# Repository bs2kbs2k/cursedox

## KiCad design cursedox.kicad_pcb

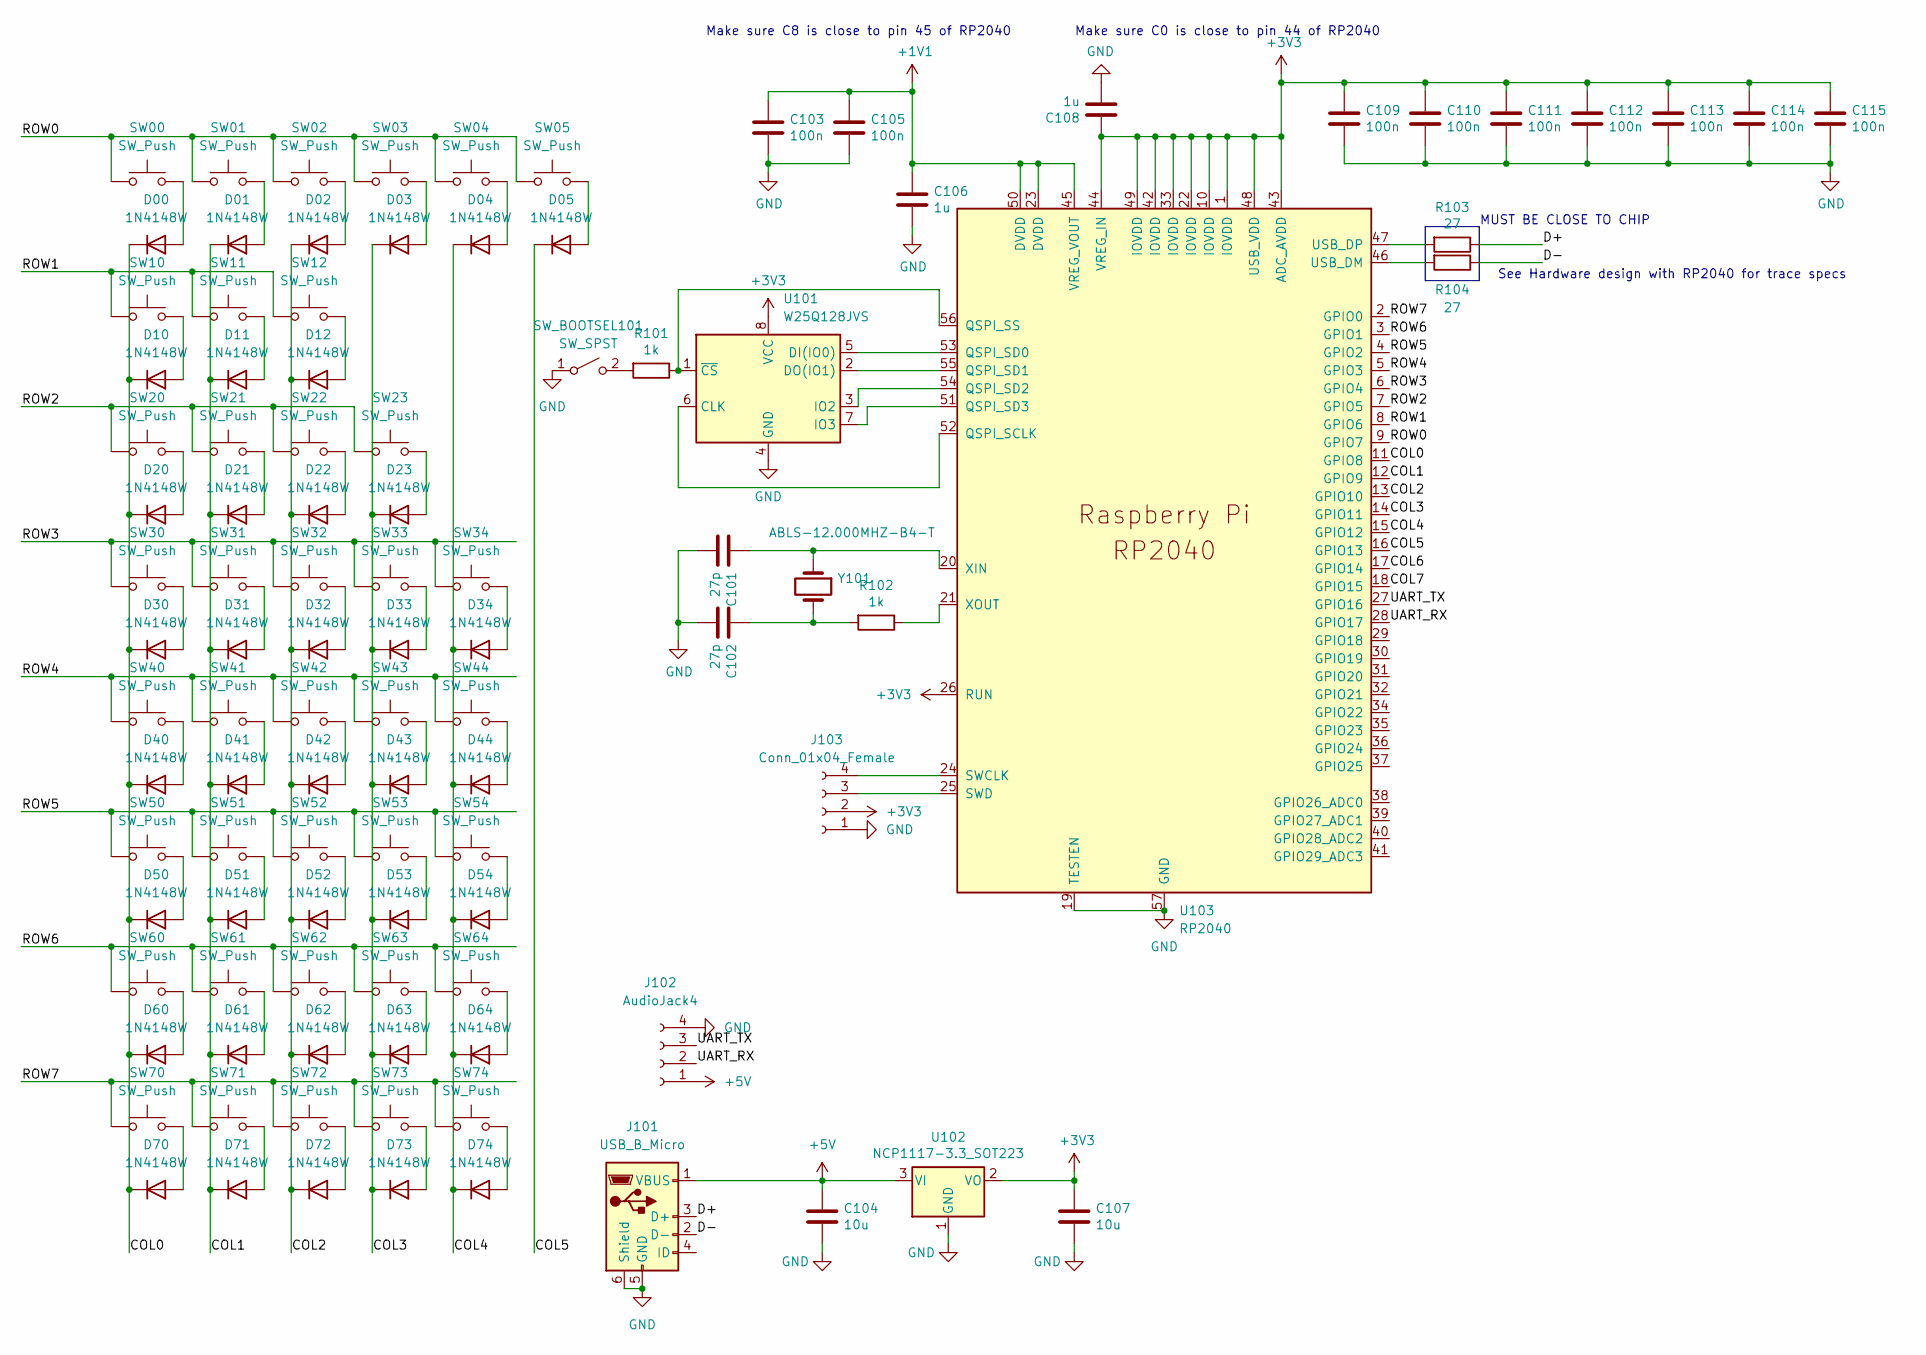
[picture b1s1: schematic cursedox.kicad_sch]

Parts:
C101, C102: 27p; C_0402_1005Metric
C103, C105, C109, C110, C111, C112, C113, C114, C115: 100n; C_0402_1005Metric
C104, C107: 10u; C_0805_2012Metric
C106, C108: 1u; C_0402_1005Metric
D00, D01, D02, D03, D04, D05, D10, D11, D12, D20, D21, D22, D23, D30, D31, D32, D33, D34, D40, D41, D42, D43, D44, D50, D51, D52, D53, D54, D60, D61, D62, D63, D64, D70, D71, D72, D73, D74: 1N4148W; D_SOD-123
J101: USB_B_Micro; USB_Micro-B_Molex-105017-0001
J102: AudioJack4; Molex_Pico-Clasp_202396-0407_1x04-1MP_P1.00mm_Horizontal
J103: Conn_01x04_Female; PinHeader_1x04_P2.54mm_Vertical
R101, R102: 1k; C_0402_1005Metric
R103, R104: 27; C_0402_1005Metric
SW00, SW01, SW02, SW03, SW10, SW20, SW21, SW22, SW23, SW30, SW31, SW32, SW33, SW34, SW40, SW41, SW42, SW43, SW44, SW50, SW51, SW52, SW53, SW54, SW60, SW61, SW62, SW63, SW64, SW74: SW_Push; SW_Hotswap_Kailh_MX_1.00u
SW04, SW05: SW_Push; SW_Hotswap_Kailh_MX_2.00u_90deg
SW11, SW12: SW_Push; SW_Hotswap_Kailh_MX_1.50u_90deg
SW70, SW71, SW72, SW73: SW_Push; SW_Hotswap_Kailh_MX_1.50u
SW_BOOTSEL101: SW_SPST; SW_TH_Tactile_Omron_B3F-10xx
U101: W25Q128JVS; SOIC-8_5.23x5.23mm_P1.27mm
U102: NCP1117-3.3_SOT223; SOT-223-3_TabPin2
U103: RP2040; RP2040-QFN-56
Y101: ABLS-12.000MHZ-B4-T; Crystal_SMD_HC49-US

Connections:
+1V1: C103.1, C105.1, C106.1, U103.23 (DVDD), U103.45 (VREG_VOUT), U103.50 (DVDD)
+3V3: C107.1, C108.1, C109.1, C110.1, C111.1, C112.1, C113.1, C114.1, C115.1, J103.2, U101.8 (VCC), U102.2 (VO), U103.1 (IOVDD), U103.10 (IOVDD), U103.22 (IOVDD), U103.26 (RUN), U103.33 (IOVDD), U103.42 (IOVDD), U103.43 (ADC_AVDD), U103.44 (VREG_IN), U103.48 (USB_VDD), U103.49 (IOVDD)
+5V: C104.1, J101.1 (VBUS), J102.1, U102.3 (VI)
/COL0: D00.1 (K), D10.1 (K), D20.1 (K), D30.1 (K), D40.1 (K), D50.1 (K), D60.1 (K), D70.1 (K), U103.11 (GPIO8)
/COL1: D01.1 (K), D11.1 (K), D21.1 (K), D31.1 (K), D41.1 (K), D51.1 (K), D61.1 (K), D71.1 (K), U103.12 (GPIO9)
/COL2: D02.1 (K), D12.1 (K), D22.1 (K), D32.1 (K), D42.1 (K), D52.1 (K), D62.1 (K), D72.1 (K), U103.13 (GPIO10)
/COL3: D03.1 (K), D23.1 (K), D33.1 (K), D43.1 (K), D53.1 (K), D63.1 (K), D73.1 (K), U103.14 (GPIO11)
/COL4: D04.1 (K), D34.1 (K), D44.1 (K), D54.1 (K), D64.1 (K), D74.1 (K), U103.15 (GPIO12)
/COL5: D05.1 (K), U103.16 (GPIO13)
/COL6: U103.17 (GPIO14)
/COL7: U103.18 (GPIO15)
/D+: J101.3 (D+), R103.1
/D-: J101.2 (D-), R104.1
/ROW0: SW00.1, SW01.1, SW02.1, SW03.1, SW04.1, SW05.1, U103.9 (GPIO7)
/ROW1: SW10.1, SW11.1, SW12.1, U103.8 (GPIO6)
/ROW2: SW20.1, SW21.1, SW22.1, SW23.1, U103.7 (GPIO5)
/ROW3: SW30.1, SW31.1, SW32.1, SW33.1, SW34.1, U103.6 (GPIO4)
/ROW4: SW40.1, SW41.1, SW42.1, SW43.1, SW44.1, U103.5 (GPIO3)
/ROW5: SW50.1, SW51.1, SW52.1, SW53.1, SW54.1, U103.4 (GPIO2)
/ROW6: SW60.1, SW61.1, SW62.1, SW63.1, SW64.1, U103.3 (GPIO1)
/ROW7: SW70.1, SW71.1, SW72.1, SW73.1, SW74.1, U103.2 (GPIO0)
/UART_RX: J102.2, U103.28 (GPIO17)
/UART_TX: J102.3, U103.27 (GPIO16)
GND: C101.2, C102.2, C103.2, C104.2, C105.2, C106.2, C107.2, C108.2, C109.2, C110.2, C111.2, C112.2, C113.2, C114.2, C115.2, J101.5 (GND), J101.6 (Shield), J102.4, J103.1, SW_BOOTSEL101.1 (A), U101.4 (GND), U102.1 (GND), U103.19 (TESTEN), U103.57 (GND)
unnamed: C101.1, U103.20 (XIN), Y101.1
unnamed: C102.1, R102.2, Y101.2
unnamed: D00.2 (A), SW00.2
unnamed: D01.2 (A), SW01.2
unnamed: D02.2 (A), SW02.2
unnamed: D03.2 (A), SW03.2
unnamed: D04.2 (A), SW04.2
unnamed: D05.2 (A), SW05.2
unnamed: D10.2 (A), SW10.2
unnamed: D11.2 (A), SW11.2
unnamed: D12.2 (A), SW12.2
unnamed: D20.2 (A), SW20.2
unnamed: D21.2 (A), SW21.2
unnamed: D22.2 (A), SW22.2
unnamed: D23.2 (A), SW23.2
unnamed: D30.2 (A), SW30.2
unnamed: D31.2 (A), SW31.2
unnamed: D32.2 (A), SW32.2
unnamed: D33.2 (A), SW33.2
unnamed: D34.2 (A), SW34.2
unnamed: D40.2 (A), SW40.2
unnamed: D41.2 (A), SW41.2
unnamed: D42.2 (A), SW42.2
unnamed: D43.2 (A), SW43.2
unnamed: D44.2 (A), SW44.2
unnamed: D50.2 (A), SW50.2
unnamed: D51.2 (A), SW51.2
unnamed: D52.2 (A), SW52.2
unnamed: D53.2 (A), SW53.2
unnamed: D54.2 (A), SW54.2
unnamed: D60.2 (A), SW60.2
unnamed: D61.2 (A), SW61.2
unnamed: D62.2 (A), SW62.2
unnamed: D63.2 (A), SW63.2
unnamed: D64.2 (A), SW64.2
unnamed: D70.2 (A), SW70.2
unnamed: D71.2 (A), SW71.2
unnamed: D72.2 (A), SW72.2
unnamed: D73.2 (A), SW73.2
unnamed: D74.2 (A), SW74.2
unnamed: J103.3, U103.25 (SWD)
unnamed: J103.4, U103.24 (SWCLK)
unnamed: R101.1, U101.1 (~CS), U103.56 (QSPI_SS)
unnamed: R101.2, SW_BOOTSEL101.2 (B)
unnamed: R102.1, U103.21 (XOUT)
unnamed: R103.2, U103.47 (USB_DP)
unnamed: R104.2, U103.46 (USB_DM)
unnamed: U101.2 (DO(IO1)), U103.55 (QSPI_SD1)
unnamed: U101.3 (IO2), U103.54 (QSPI_SD2)
unnamed: U101.5 (DI(IO0)), U103.53 (QSPI_SD0)
unnamed: U101.6 (CLK), U103.52 (QSPI_SCLK)
unnamed: U101.7 (IO3), U103.51 (QSPI_SD3)

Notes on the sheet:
See Hardware design with RP2040 for trace specs
MUST BE CLOSE TO CHIP
Make sure C0 is close to pin 44 of RP2040
Make sure C8 is close to pin 45 of RP2040

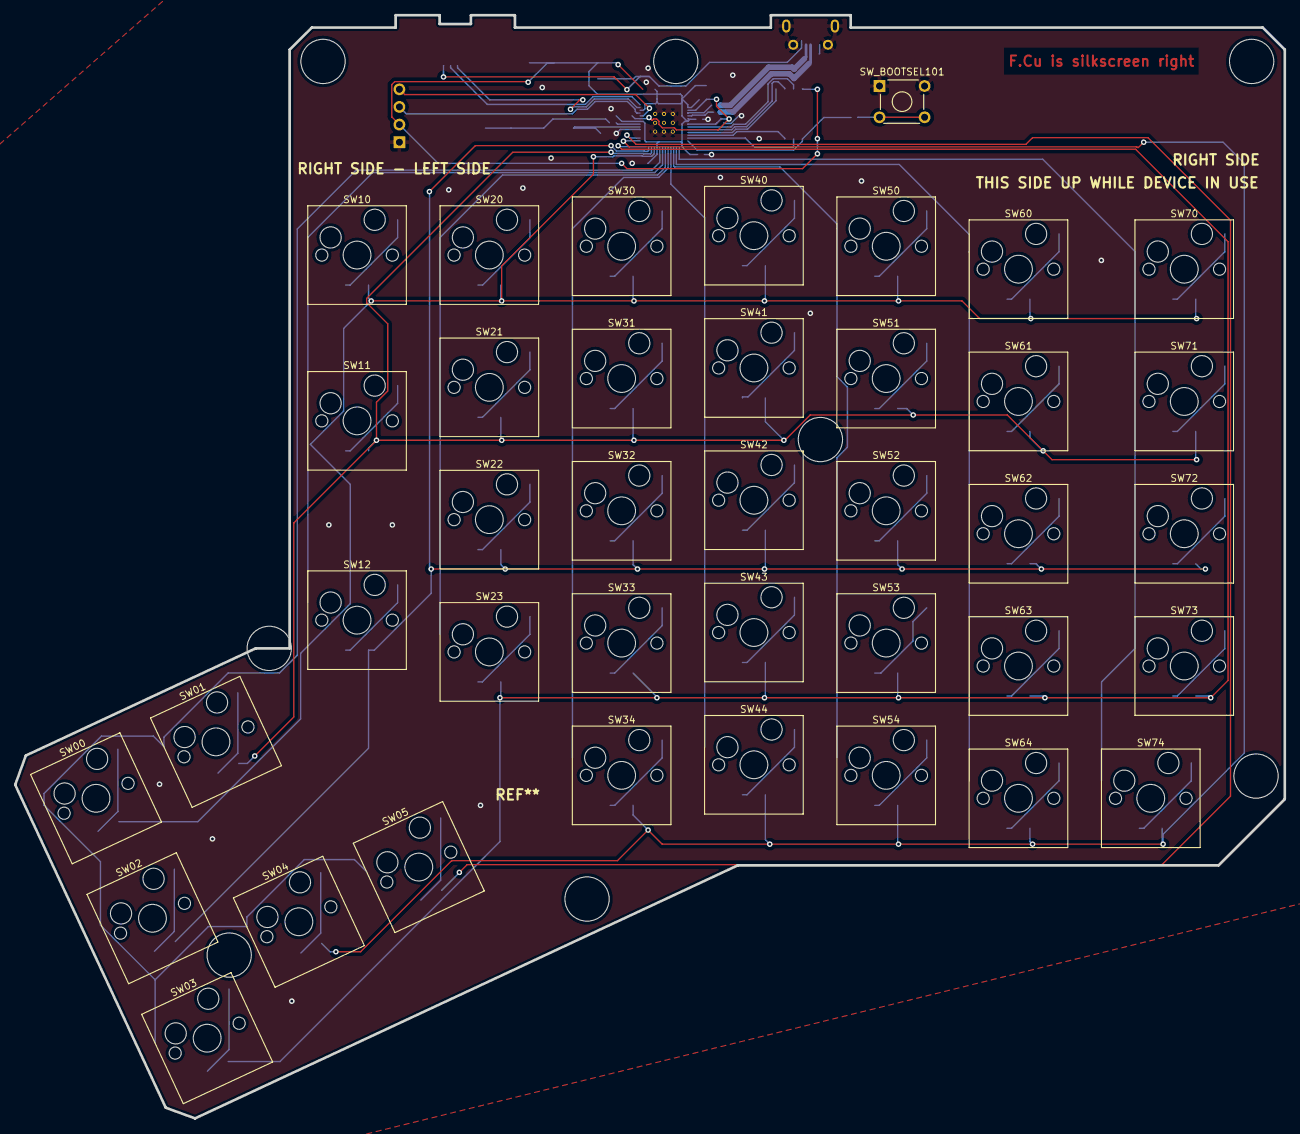
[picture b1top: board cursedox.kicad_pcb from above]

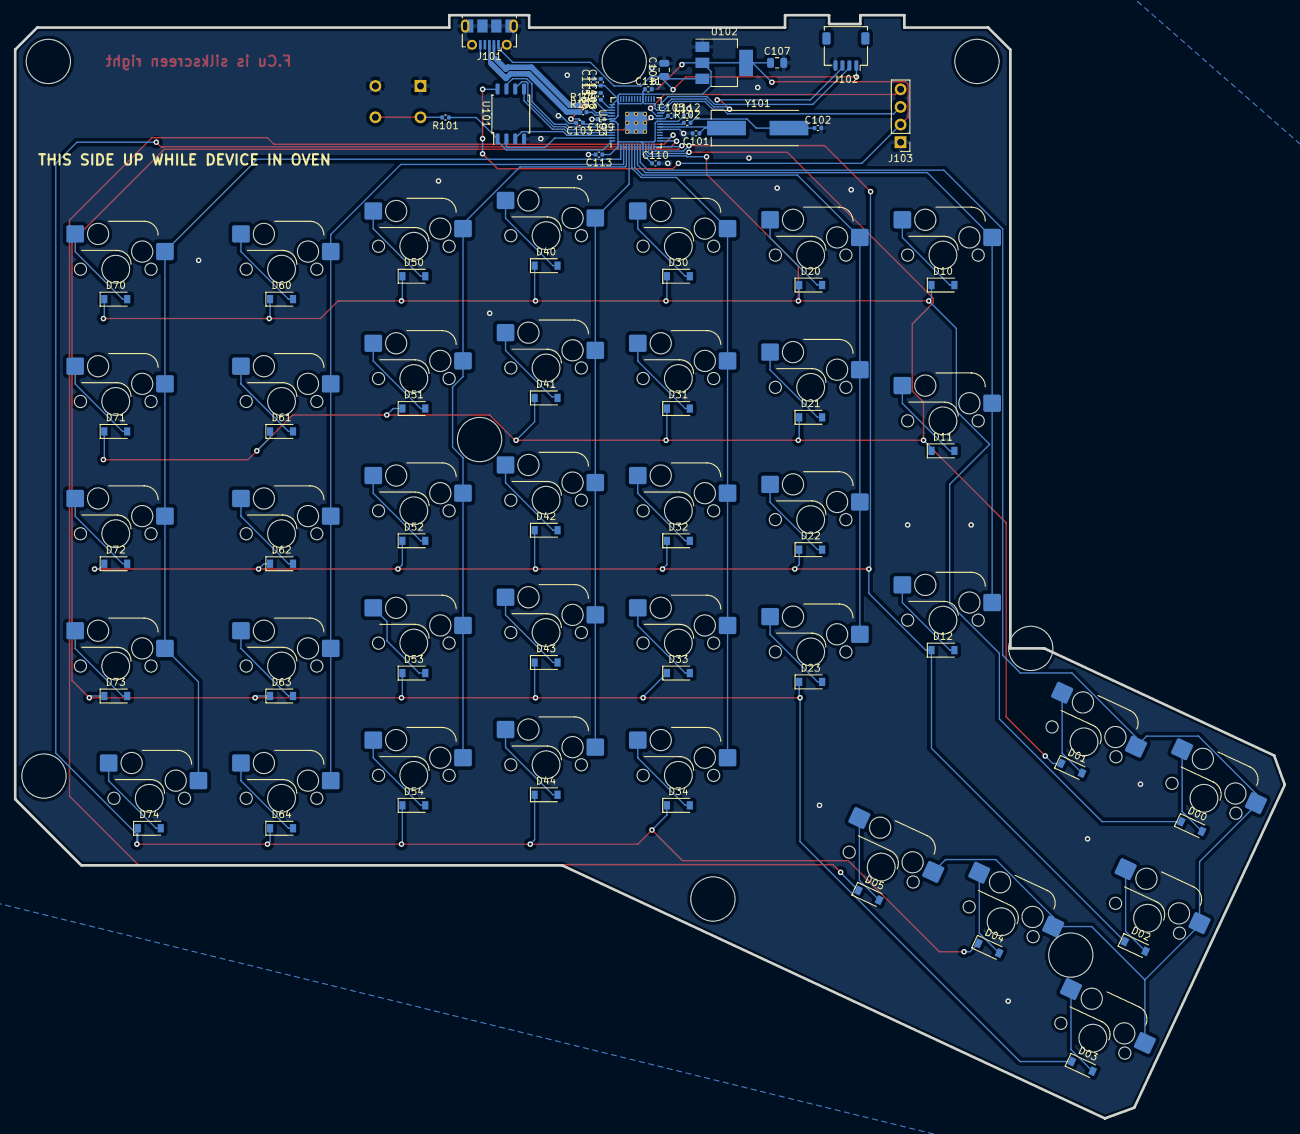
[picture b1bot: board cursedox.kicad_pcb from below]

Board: 2 copper layers, 182.8 x 158.9 mm, 104 parts (64 on the bottom side), 74 nets.

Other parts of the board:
H99: MECHANICAL; ErgoDOXmech

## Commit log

2022-07-08 asdf
